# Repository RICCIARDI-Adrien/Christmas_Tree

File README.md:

# Christmas tree

A lighted Christmas tree with shiny fairy lights and star.  

Here are all needed parts to build the Christmas tree :  

## Hardware

Board has been designed with KiCaD 5.1.4.
* PCB production files and Bill of materials are available in [releases](https://github.com/RICCIARDI-Adrien/Christmas_Tree/releases) section.
* When manufacturing the PCB, select a black top and bottom solder mask to highlight the leds.
* Board is powered by an USB-B connector. Use a 2A (or more) standard USB power supply, like [this one](https://fr.rs-online.com/web/p/adaptateurs-ac-dc/1242193/).

## Software

Software is written in C for Microchip XC8 compiler. It works with free compiler version.

To build the firmware, go to `Software` directory and type `make`.

## Casing

Casing and supports are made of 3mm-thick galvanized steel. A DXF file is provided in [releases](https://github.com/RICCIARDI-Adrien/Christmas_Tree/releases) section for laser cutting.

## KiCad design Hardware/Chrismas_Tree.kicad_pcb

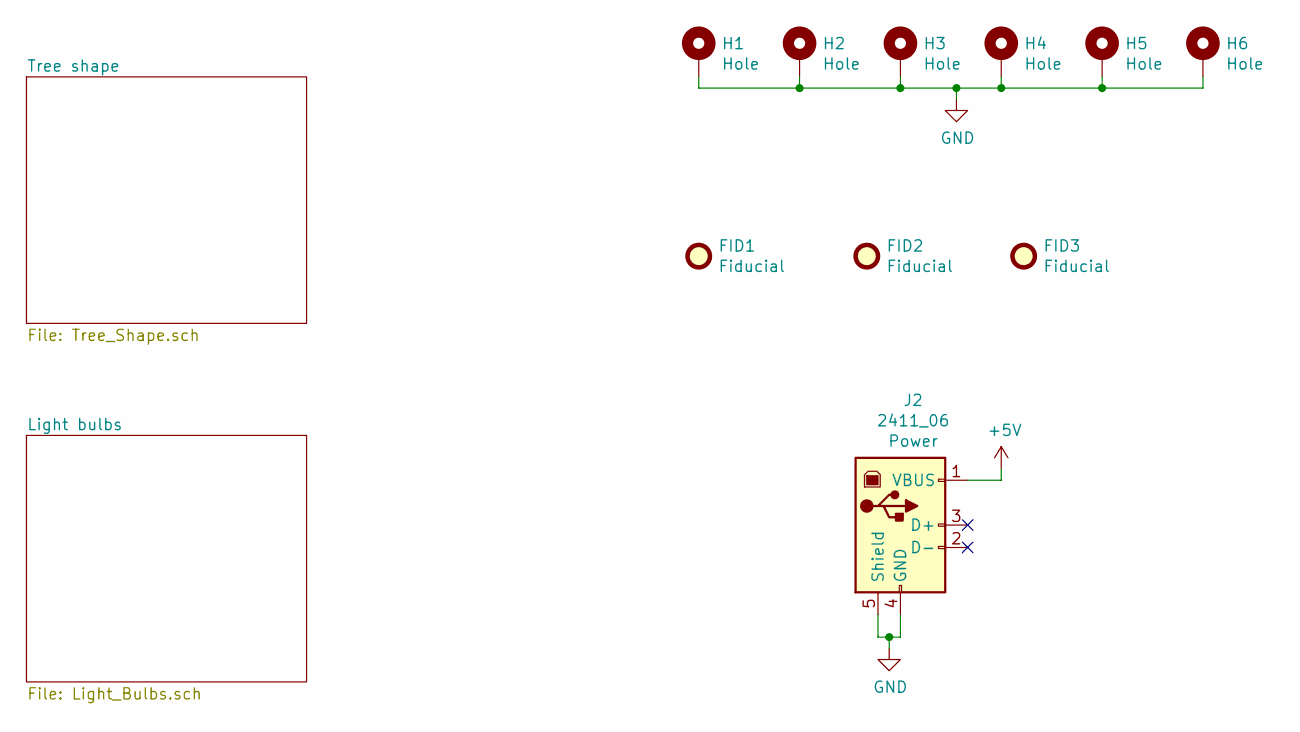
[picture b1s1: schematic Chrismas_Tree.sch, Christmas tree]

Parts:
FID1, FID2, FID3: Fiducial; Fiducial_1.5mm_Mask3mm
H1, H2, H3, H4, H5, H6: Hole; MountingHole_4.5mm_Pad
J2: 2411_06; USB_B_OST_USB-B1HSxx_Horizontal

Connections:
+5V: J2.1 (VBUS); also elsewhere on the board
GND: H1.1, H2.1, H3.1, H4.1, H5.1, H6.1, J2.4 (GND), J2.5 (Shield); also elsewhere on the board

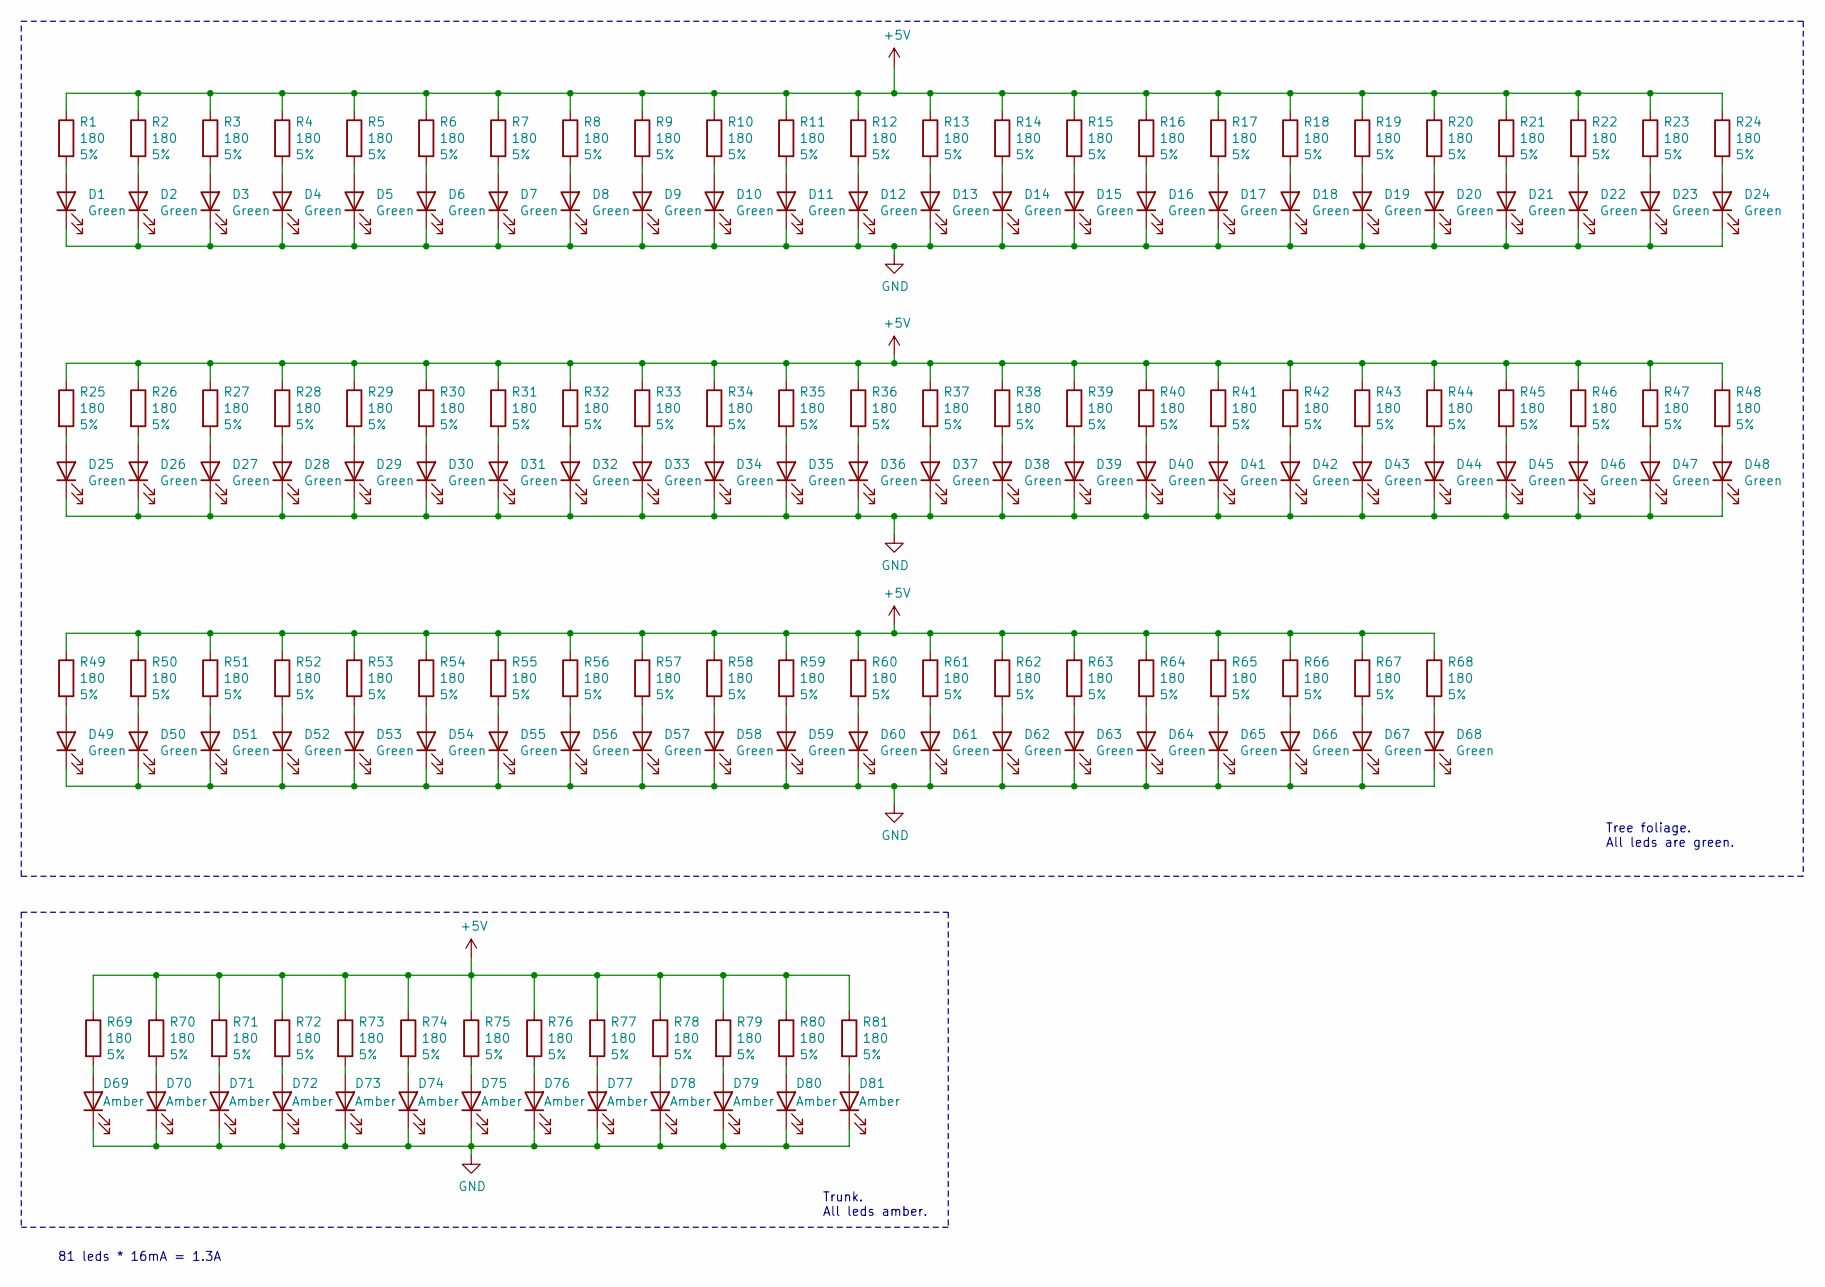
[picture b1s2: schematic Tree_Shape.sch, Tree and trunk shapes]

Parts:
D1, D2, D3, D4, D5, D6, D7, D8, D9, D10, D11, D12, D13, D14, D15, D16, D17, D18, D19, D20, D21, D22, D23, D24, D25, D26, D27, D28, D29, D30, D31, D32, D33, D34, D35, D36, D37, D38, D39, D40, D41, D42, D43, D44, D45, D46, D47, D48, D49, D50, D51, D52, D53, D54, D55, D56, D57, D58, D59, D60, D61, D62, D63, D64, D65, D66, D67, D68: Green; LED_D5.0mm
D69, D70, D71, D72, D73, D74, D75, D76, D77, D78, D79, D80, D81: Amber; LED_D5.0mm
R1, R2, R3, R4, R5, R6, R7, R8, R9, R10, R11, R12, R13, R14, R15, R16, R17, R18, R19, R20, R21, R22, R23, R24, R25, R26, R27, R28, R29, R30, R31, R32, R33, R34, R35, R36, R37, R38, R39, R40, R41, R42, R43, R44, R45, R46, R47, R48, R49, R50, R51, R52, R53, R54, R55, R56, R57, R58, R59, R60, R61, R62, R63, R64, R65, R66, R67, R68, R69, R70, R71, R72, R73, R74, R75, R76, R77, R78, R79, R80, R81: 180; R_1206_3216Metric_Pad1.30x1.75mm_HandSolder

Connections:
+5V: R1.1, R2.1, R3.1, R4.1, R5.1, R6.1, R7.1, R8.1, R9.1, R10.1, R11.1, R12.1, R13.1, R14.1, R15.1, R16.1, R17.1, R18.1, R19.1, R20.1, R21.1, R22.1, R23.1, R24.1, R25.1, R26.1, R27.1, R28.1, R29.1, R30.1, R31.1, R32.1, R33.1, R34.1, R35.1, R36.1, R37.1, R38.1, R39.1, R40.1, R41.1, R42.1, R43.1, R44.1, R45.1, R46.1, R47.1, R48.1, R49.1, R50.1, R51.1, R52.1, R53.1, R54.1, R55.1, R56.1, R57.1, R58.1, R59.1, R60.1, R61.1, R62.1, R63.1, R64.1, R65.1, R66.1, R67.1, R68.1, R69.1, R70.1, R71.1, R72.1, R73.1, R74.1, R75.1, R76.1, R77.1, R78.1, R79.1, R80.1, R81.1; also elsewhere on the board
GND: D1.1 (K), D2.1 (K), D3.1 (K), D4.1 (K), D5.1 (K), D6.1 (K), D7.1 (K), D8.1 (K), D9.1 (K), D10.1 (K), D11.1 (K), D12.1 (K), D13.1 (K), D14.1 (K), D15.1 (K), D16.1 (K), D17.1 (K), D18.1 (K), D19.1 (K), D20.1 (K), D21.1 (K), D22.1 (K), D23.1 (K), D24.1 (K), D25.1 (K), D26.1 (K), D27.1 (K), D28.1 (K), D29.1 (K), D30.1 (K), D31.1 (K), D32.1 (K), D33.1 (K), D34.1 (K), D35.1 (K), D36.1 (K), D37.1 (K), D38.1 (K), D39.1 (K), D40.1 (K), D41.1 (K), D42.1 (K), D43.1 (K), D44.1 (K), D45.1 (K), D46.1 (K), D47.1 (K), D48.1 (K), D49.1 (K), D50.1 (K), D51.1 (K), D52.1 (K), D53.1 (K), D54.1 (K), D55.1 (K), D56.1 (K), D57.1 (K), D58.1 (K), D59.1 (K), D60.1 (K), D61.1 (K), D62.1 (K), D63.1 (K), D64.1 (K), D65.1 (K), D66.1 (K), D67.1 (K), D68.1 (K), D69.1 (K), D70.1 (K), D71.1 (K), D72.1 (K), D73.1 (K), D74.1 (K), D75.1 (K), D76.1 (K), D77.1 (K), D78.1 (K), D79.1 (K), D80.1 (K), D81.1 (K); also elsewhere on the board
unnamed: D1.2 (A), R1.2
unnamed: D2.2 (A), R2.2
unnamed: D3.2 (A), R3.2
unnamed: D4.2 (A), R4.2
unnamed: D5.2 (A), R5.2
unnamed: D6.2 (A), R6.2
unnamed: D7.2 (A), R7.2
unnamed: D8.2 (A), R8.2
unnamed: D9.2 (A), R9.2
unnamed: D10.2 (A), R10.2
unnamed: D11.2 (A), R11.2
unnamed: D12.2 (A), R12.2
unnamed: D13.2 (A), R13.2
unnamed: D14.2 (A), R14.2
unnamed: D15.2 (A), R15.2
unnamed: D16.2 (A), R16.2
unnamed: D17.2 (A), R17.2
unnamed: D18.2 (A), R18.2
unnamed: D19.2 (A), R19.2
unnamed: D20.2 (A), R20.2
unnamed: D21.2 (A), R21.2
unnamed: D22.2 (A), R22.2
unnamed: D23.2 (A), R23.2
unnamed: D24.2 (A), R24.2
unnamed: D25.2 (A), R25.2
unnamed: D26.2 (A), R26.2
unnamed: D27.2 (A), R27.2
unnamed: D28.2 (A), R28.2
unnamed: D29.2 (A), R29.2
unnamed: D30.2 (A), R30.2
unnamed: D31.2 (A), R31.2
unnamed: D32.2 (A), R32.2
unnamed: D33.2 (A), R33.2
unnamed: D34.2 (A), R34.2
unnamed: D35.2 (A), R35.2
unnamed: D36.2 (A), R36.2
unnamed: D37.2 (A), R37.2
unnamed: D38.2 (A), R38.2
unnamed: D39.2 (A), R39.2
unnamed: D40.2 (A), R40.2
unnamed: D41.2 (A), R41.2
unnamed: D42.2 (A), R42.2
unnamed: D43.2 (A), R43.2
unnamed: D44.2 (A), R44.2
unnamed: D45.2 (A), R45.2
unnamed: D46.2 (A), R46.2
unnamed: D47.2 (A), R47.2
unnamed: D48.2 (A), R48.2
unnamed: D49.2 (A), R49.2
unnamed: D50.2 (A), R50.2
unnamed: D51.2 (A), R51.2
unnamed: D52.2 (A), R52.2
unnamed: D53.2 (A), R53.2
unnamed: D54.2 (A), R54.2
unnamed: D55.2 (A), R55.2
unnamed: D56.2 (A), R56.2
unnamed: D57.2 (A), R57.2
unnamed: D58.2 (A), R58.2
unnamed: D59.2 (A), R59.2
unnamed: D60.2 (A), R60.2
unnamed: D61.2 (A), R61.2
unnamed: D62.2 (A), R62.2
unnamed: D63.2 (A), R63.2
unnamed: D64.2 (A), R64.2
unnamed: D65.2 (A), R65.2
unnamed: D66.2 (A), R66.2
unnamed: D67.2 (A), R67.2
unnamed: D68.2 (A), R68.2
unnamed: D69.2 (A), R69.2
unnamed: D70.2 (A), R70.2
unnamed: D71.2 (A), R71.2
unnamed: D72.2 (A), R72.2
unnamed: D73.2 (A), R73.2
unnamed: D74.2 (A), R74.2
unnamed: D75.2 (A), R75.2
unnamed: D76.2 (A), R76.2
unnamed: D77.2 (A), R77.2
unnamed: D78.2 (A), R78.2
unnamed: D79.2 (A), R79.2
unnamed: D80.2 (A), R80.2
unnamed: D81.2 (A), R81.2

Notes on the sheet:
Tree foliage. All leds are green.
Trunk. All leds amber.
81 leds * 16mA = 1.3A

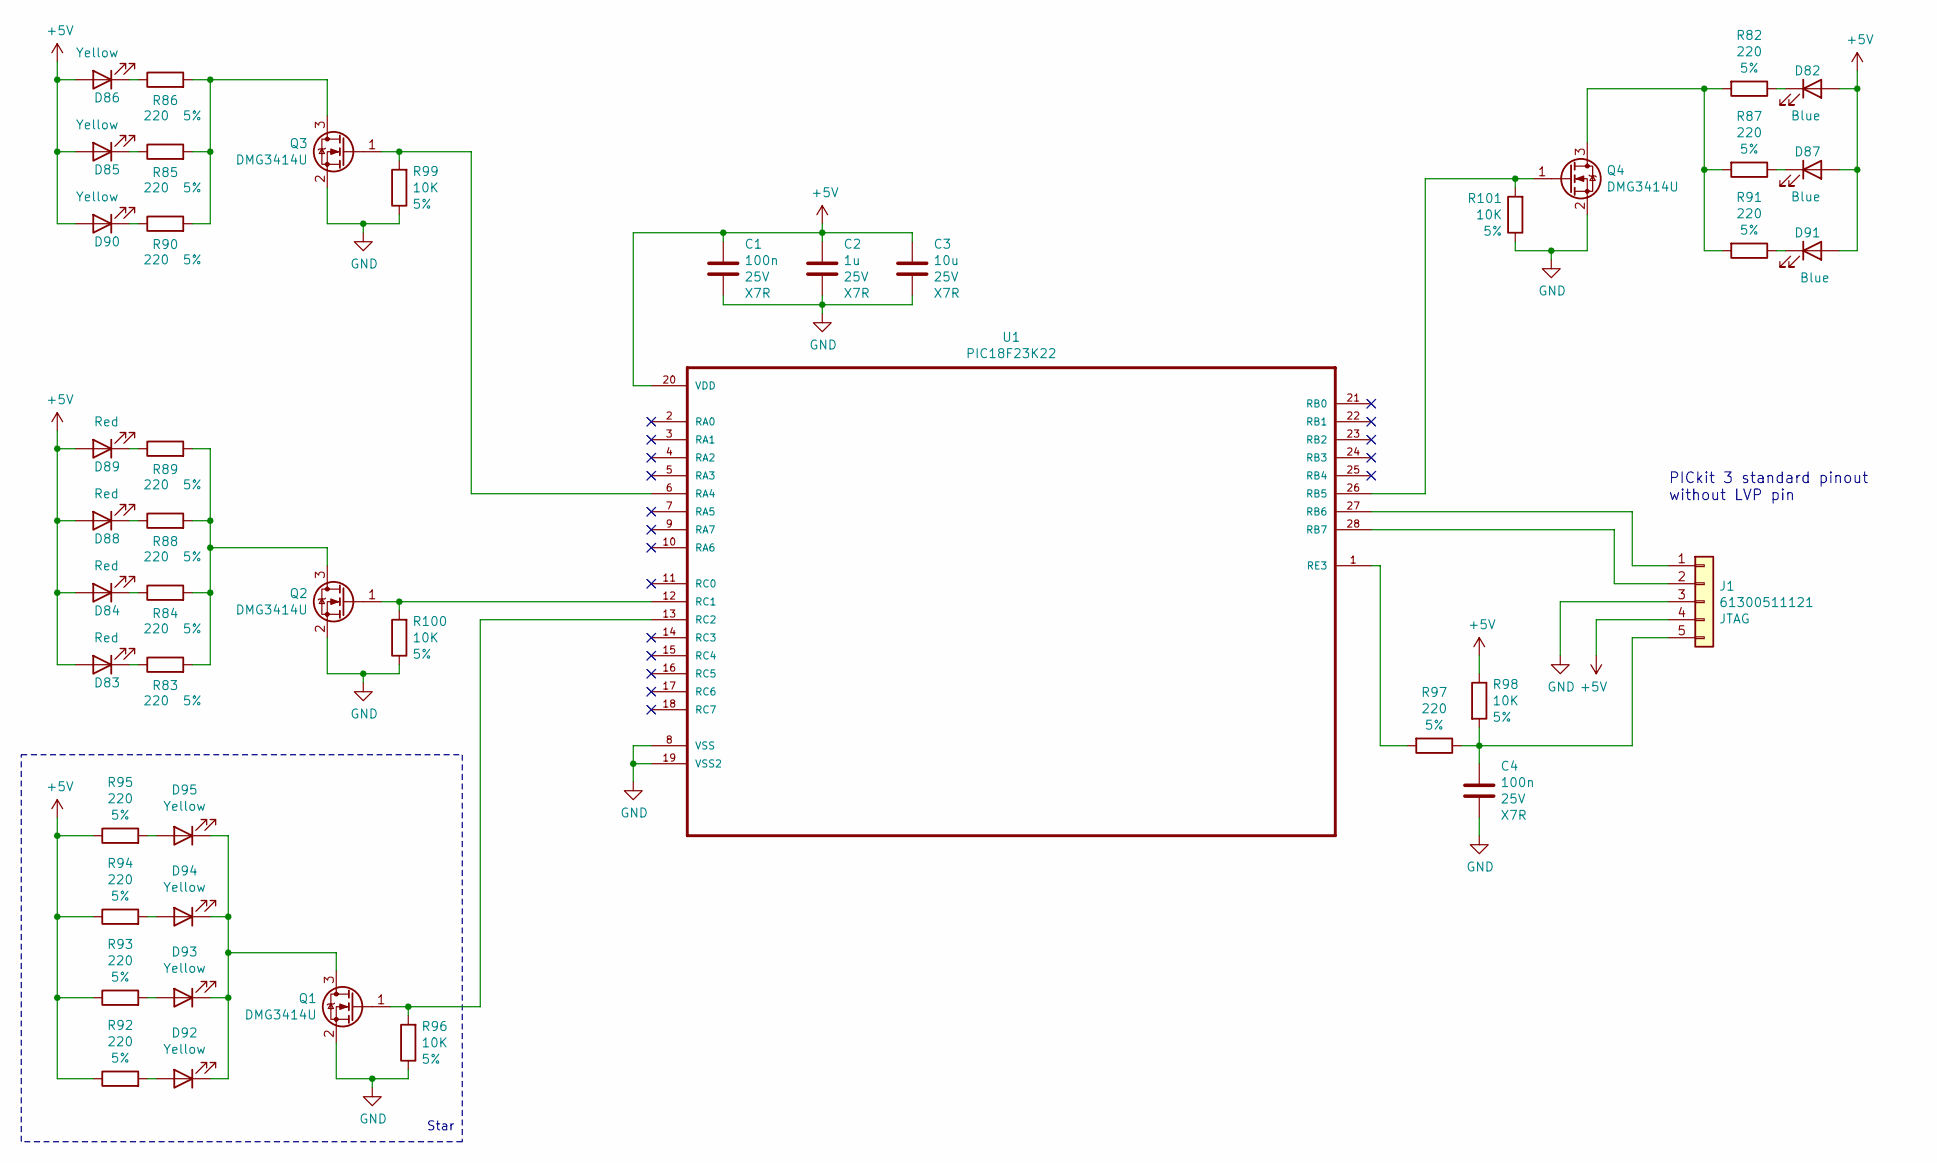
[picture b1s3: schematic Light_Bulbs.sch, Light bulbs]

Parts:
C1, C4: 100n; C_1206_3216Metric_Pad1.33x1.80mm_HandSolder
C2: 1u; C_1206_3216Metric_Pad1.33x1.80mm_HandSolder
C3: 10u; C_1206_3216Metric_Pad1.33x1.80mm_HandSolder
D82, D87, D91: Blue; LED_D5.0mm
D83, D84, D88, D89: Red; LED_D5.0mm
D85, D86, D90, D92, D93, D94, D95: Yellow; LED_D5.0mm
J1: 61300511121; PinHeader_1x05_P2.54mm_Vertical
Q1, Q2, Q3, Q4: DMG3414U; SOT-23
R82, R83, R84, R85, R86, R87, R88, R89, R90, R91, R92, R93, R94, R95, R97: 220; R_1206_3216Metric_Pad1.30x1.75mm_HandSolder
R96, R98, R99, R100, R101: 10K; R_1206_3216Metric_Pad1.30x1.75mm_HandSolder
U1: PIC18F23K22; SOIC-28W_7.5x17.9mm_P1.27mm

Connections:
+5V: C1.1, C2.1, C3.1, D82.2 (A), D83.2 (A), D84.2 (A), D85.2 (A), D86.2 (A), D87.2 (A), D88.2 (A), D89.2 (A), D90.2 (A), D91.2 (A), J1.4, R92.1, R93.1, R94.1, R95.1, R98.1, U1.20 (VDD); also elsewhere on the board
GND: C1.2, C2.2, C3.2, C4.2, J1.3, Q1.2 (S), Q2.2 (S), Q3.2 (S), Q4.2 (S), R96.1, R99.1, R100.1, R101.1, U1.8 (VSS), U1.19 (VSS2); also elsewhere on the board
unnamed: C4.1, J1.5, R97.1, R98.2
unnamed: D82.1 (K), R82.1
unnamed: D83.1 (K), R83.1
unnamed: D84.1 (K), R84.1
unnamed: D85.1 (K), R85.1
unnamed: D86.1 (K), R86.1
unnamed: D87.1 (K), R87.1
unnamed: D88.1 (K), R88.1
unnamed: D89.1 (K), R89.1
unnamed: D90.1 (K), R90.1
unnamed: D91.1 (K), R91.1
unnamed: D92.1 (K), D93.1 (K), D94.1 (K), D95.1 (K), Q1.3 (D)
unnamed: D92.2 (A), R92.2
unnamed: D93.2 (A), R93.2
unnamed: D94.2 (A), R94.2
unnamed: D95.2 (A), R95.2
unnamed: J1.1, U1.27 (RB6)
unnamed: J1.2, U1.28 (RB7)
unnamed: Q1.1 (G), R96.2, U1.13 (RC2)
unnamed: Q2.1 (G), R100.2, U1.12 (RC1)
unnamed: Q2.3 (D), R83.2, R84.2, R88.2, R89.2
unnamed: Q3.1 (G), R99.2, U1.6 (RA4)
unnamed: Q3.3 (D), R85.2, R86.2, R90.2
unnamed: Q4.1 (G), R101.2, U1.26 (RB5)
unnamed: Q4.3 (D), R82.2, R87.2, R91.2
unnamed: R97.2, U1.1 (RE3)

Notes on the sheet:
PICkit 3 standard pinout without LVP pin
Star

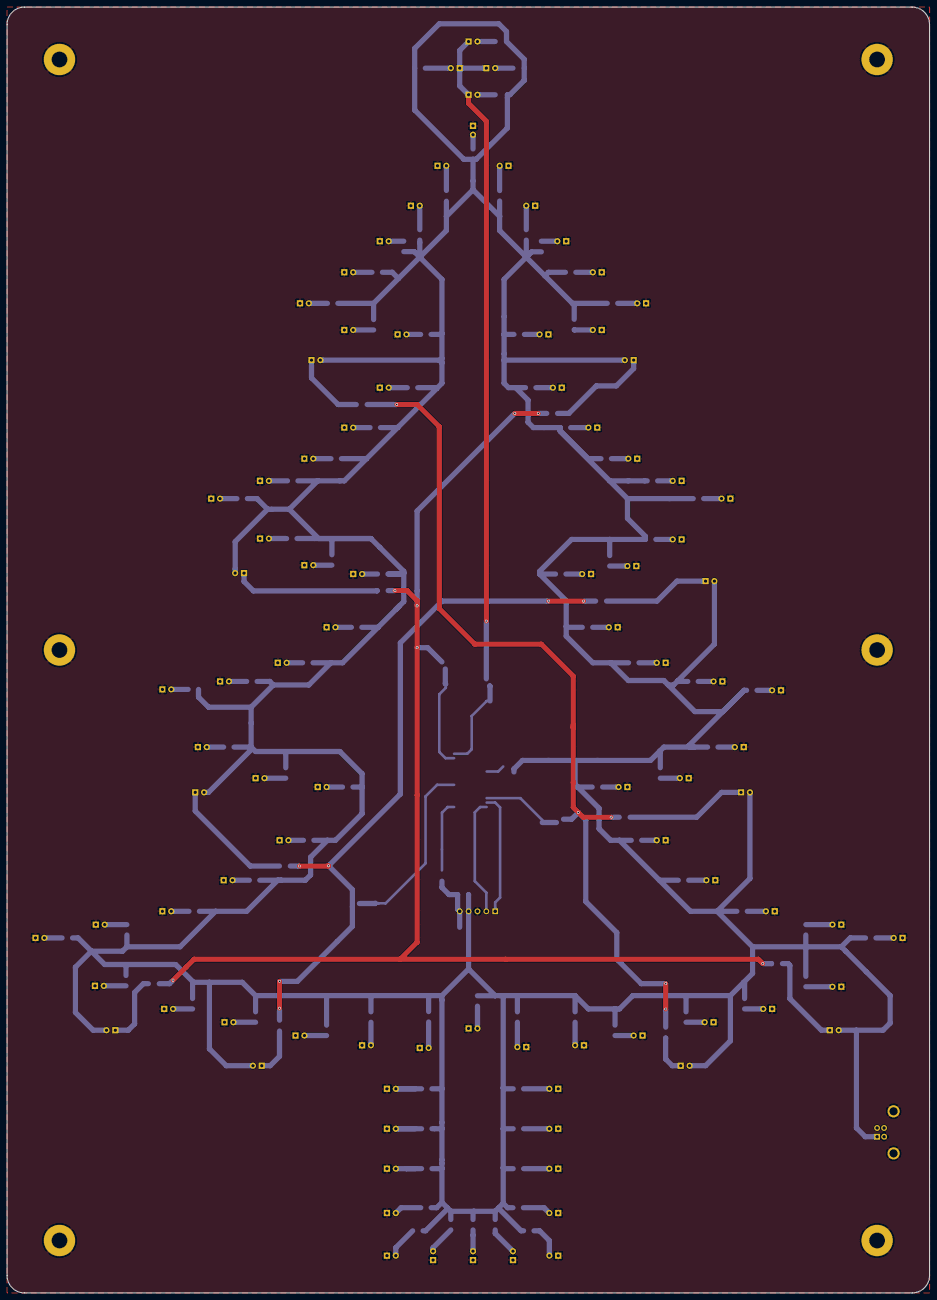
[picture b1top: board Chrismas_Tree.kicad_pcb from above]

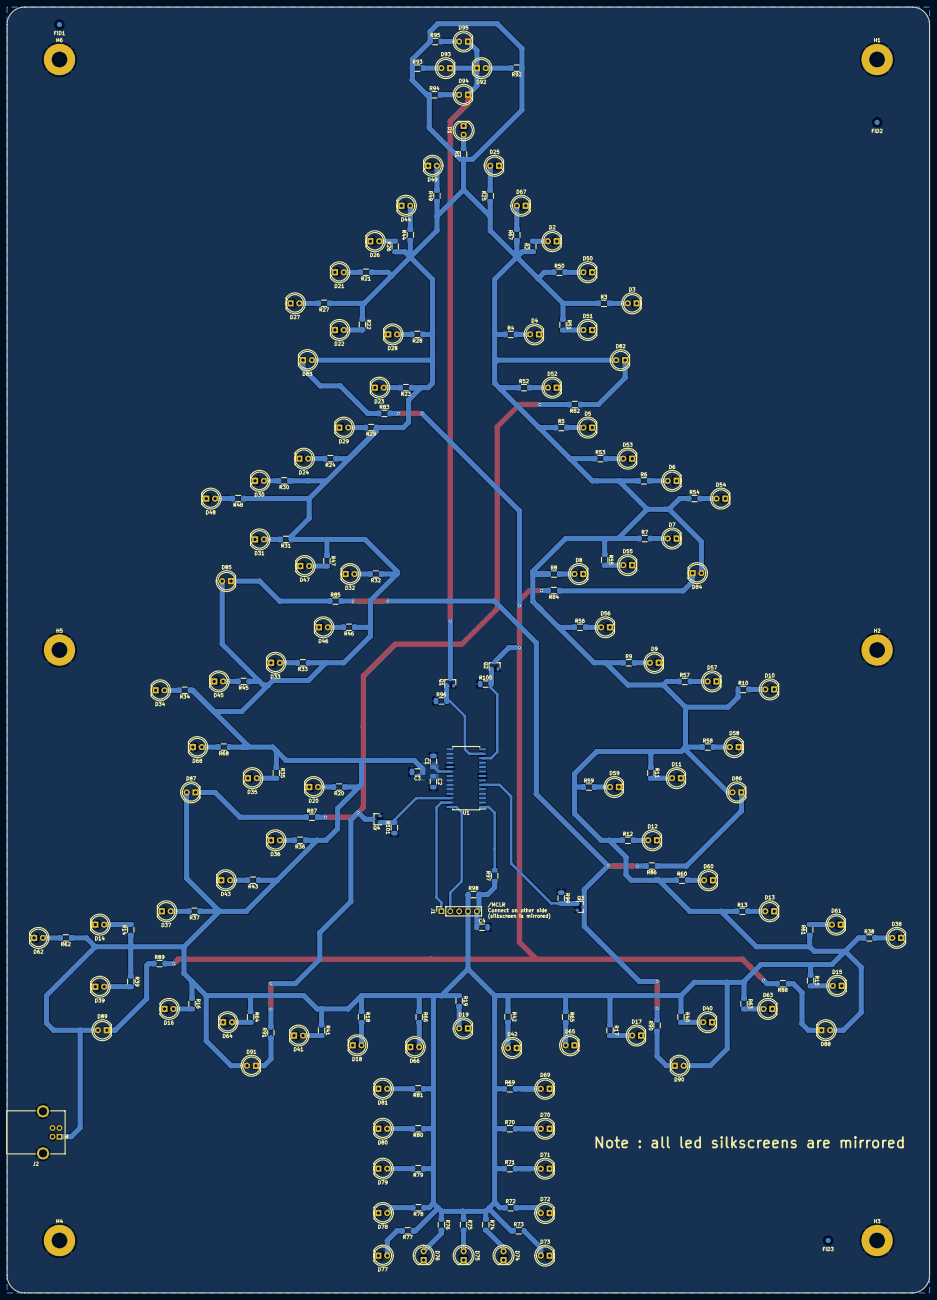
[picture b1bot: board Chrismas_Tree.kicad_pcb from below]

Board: 2 copper layers, 264.0 x 368.0 mm, 216 parts (114 on the bottom side), 109 nets.

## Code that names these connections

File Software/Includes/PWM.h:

/** @file PWM.h
 * Manage 4 separate PWM channels, one for each tree fading block.
 * @author Adrien RICCIARDI
 */
#ifndef H_PWM_H
#define H_PWM_H

//-------------------------------------------------------------------------------------------------
// Constants
//-------------------------------------------------------------------------------------------------
/** Maximum PWM duty cycle period. When setting this period, the PWM pin is always set. */
#define PWM_MAXIMUM_DUTY_CYCLE_VALUE 1023

//-------------------------------------------------------------------------------------------------
// Types
//-------------------------------------------------------------------------------------------------
/** All available channels. */
typedef enum
{
	PWM_CHANNEL_ID_STAR, // Use CCP1 module on RC2 pin
	PWM_CHANNEL_ID_RED_FAIRY_LIGHTS, // Use CCP2 module on RC1 pin
	PWM_CHANNEL_ID_BLUE_FAIRY_LIGHTS, // Use CCP3 module on RB5 pin
	PWM_CHANNEL_ID_YELLOW_FAIRY_LIGHTS, // Use CCP5 module on RA4 pin
	PWM_CHANNEL_IDS_COUNT
} TPWMChannelID;

//-------------------------------------------------------------------------------------------------
// Functions
//-------------------------------------------------------------------------------------------------
/** Initialize all PWM channels and start producing signals. */
void PWMInitialize(void);

/** Set a specific channel duty cycle period.
 * @param Channel_ID The channel to configure.
 * @param Duty_Cycle_Period How many time the channel pin remains set. Setting value 0 makes the pin stay always low, setting value PWM_MAXIMUM_DUTY_CYCLE_VALUE makes the pin stay always high.
 */
void PWMSetDutyCycle(TPWMChannelID Channel_ID, unsigned short Duty_Cycle_Period);

#endif

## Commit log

2019-11-27 Initial commit. Added tree leds to schematic and designed tree shape on PCB.
2019-11-27 Added tree trunk to schematic and PCB.
2019-11-27 Reorganized schematic to use several sheets.
2019-11-27 Added microcontroller symbol and footprint.
2019-11-27 Placed all tree foliage and trunk resistors on the PCB.
2019-11-27 Moved hardware files directly to Hardware directory for more coherency.
2019-11-27 Added light bulbs schematic.
2019-11-27 Reorganized light bulbs connections to ease routing and placed microcontroller and related parts.
2019-11-27 Set foliage and trunk leds color.
2019-11-27 Set foliage leds resistors value.
2019-11-27 Set trunk leds resistors value.
2019-11-27 Added micro USB B connector for power supply.
2019-11-27 Routed whole circuit and added ground planes.
2019-11-28 Added missing microcontroller library.
2019-11-28 Used standard schematic title blocks titles.
2019-11-28 Fixed PCB title block.
2019-11-28 Added PCB edges cut.
2019-11-28 Resized board to center the tree in the PCB middle.
2019-11-28 Adjusted bottom left branch light bulbs.
2019-11-28 Added fixation holes to PCB.
2019-11-28 Increased transitor base resistor value.
2019-11-28 Added README.md.
2019-11-28 Started firmware implementation. A led is blinking.
2019-11-28 Started software PWM implementation. Added working test to access through pointer to port register.
2019-11-28 Added PWM base frequency generation.
2019-11-28 Added working software PWM.
2019-11-28 Added the ability to set PWM duty cycle period.
2019-11-28 Initialized all PWM channels in Fading Leds module.
2019-11-28 Added led shining algorithm.
2019-11-29 Added mounting holes to schematic.
2019-11-29 Started PWM module implementation.
2019-11-29 Updated schematic and PCB to use microcontroller hardware PWMs to control fairy lights by color and star instead of all light bulbs separately.
2019-11-29 Added PWM duty cycle configuration function.
2019-11-29 Adapted fading code to new PWM module.
2019-11-29 Removed now useless Fading Led module.
2019-11-29 Added some phase difference between each PWM channel to make each channel blink separately.
2019-11-30 Replaced USB micro B connector by a more robust USB B one.
2019-11-30 Made sure all leds are turned off at boot.
2019-11-30 Added casing drawing. This is not the production file to send to laser cutter because it contains PCB and flat square brackets parts.
2019-11-30 Added information about power supply to README.md.
2019-12-06 Replaced leds linear brightness variation by an exponential one to make dimming feels more linear to human eye.
2019-12-07 Removed flat angle brackets and added supports to casing.
2019-12-08 Decreased casing supports height to avoid obstructing USB connector.
2020-01-02 Decreased casing grooves thickness to decrease play between supports and casing.
2020-01-04 Added Christmas tree pictures.
2020-01-04 Added project pictures to README.md as well as more detailed technical information.
2020-01-11 Improved leds dimming by using a dimming equation better matching human eye response.
2020-02-20 Added a picture showing all needed parts.
2020-06-13 Removed unneeded 'fp-info-cache' file from repository.
2020-06-13 Replaced light bulb through-hole resistors by SMD ones.
2020-06-17 Put all amber leds in their right place.
2020-06-17 Replaced trunk through-hole resistors by SMD ones.
2020-09-18 Changed PCB copper area isolation to get a better filling.
2020-09-18 Turned rotated leds to have all them on the same axis (but trunk base ones).
2020-09-18 Replaced tree foliage through-hole resistors by SMD ones.
2020-09-18 Replaced though-hole capacitors by SMD ones.
2020-09-18 Replaced through-hole transistors by SMD ones.
2020-09-18 Removed now useless 2N2222A library.
2020-09-18 Changed microcontroller package for a SMD one.
2020-09-18 Added rounded corners to PCB, improved PCB dimensions to fit in millimeters.
2021-11-21 Updated USB connector symbol reference in schematic to conform to KiCad 5.1.10.
2021-11-21 Added USB connector 3D model to PCB.
2021-11-21 Moved mounting holes silkscreen text to bottom layer, so it is not shown on the leds side.
2021-11-21 Reset PCB solder mask settings as default ones work fine.
2021-11-21 Changed all remaining through-hole resistors by SMD ones in both schematic and PCB.
2021-11-21 Converted all 1206 SMD footprints to KiCad 5.1.10 latest one in both schematic and PCB.
2021-11-21 Moved all PCB top layer silkscreen texts to bottom layer.
2021-11-21 Updated bill of materials data on schematic to improve generated bill of materials.
2021-11-21 Adjusted mounting hole locations to fit on millimeter boundaries.
2021-11-24 Rounded casing corners with the same radius than the PCB corners. Also adapted casing mounting holes to new PCB ones.
2021-11-25 Added fiducials to PCB.
2021-11-25 Ignored PCB generated output files.
